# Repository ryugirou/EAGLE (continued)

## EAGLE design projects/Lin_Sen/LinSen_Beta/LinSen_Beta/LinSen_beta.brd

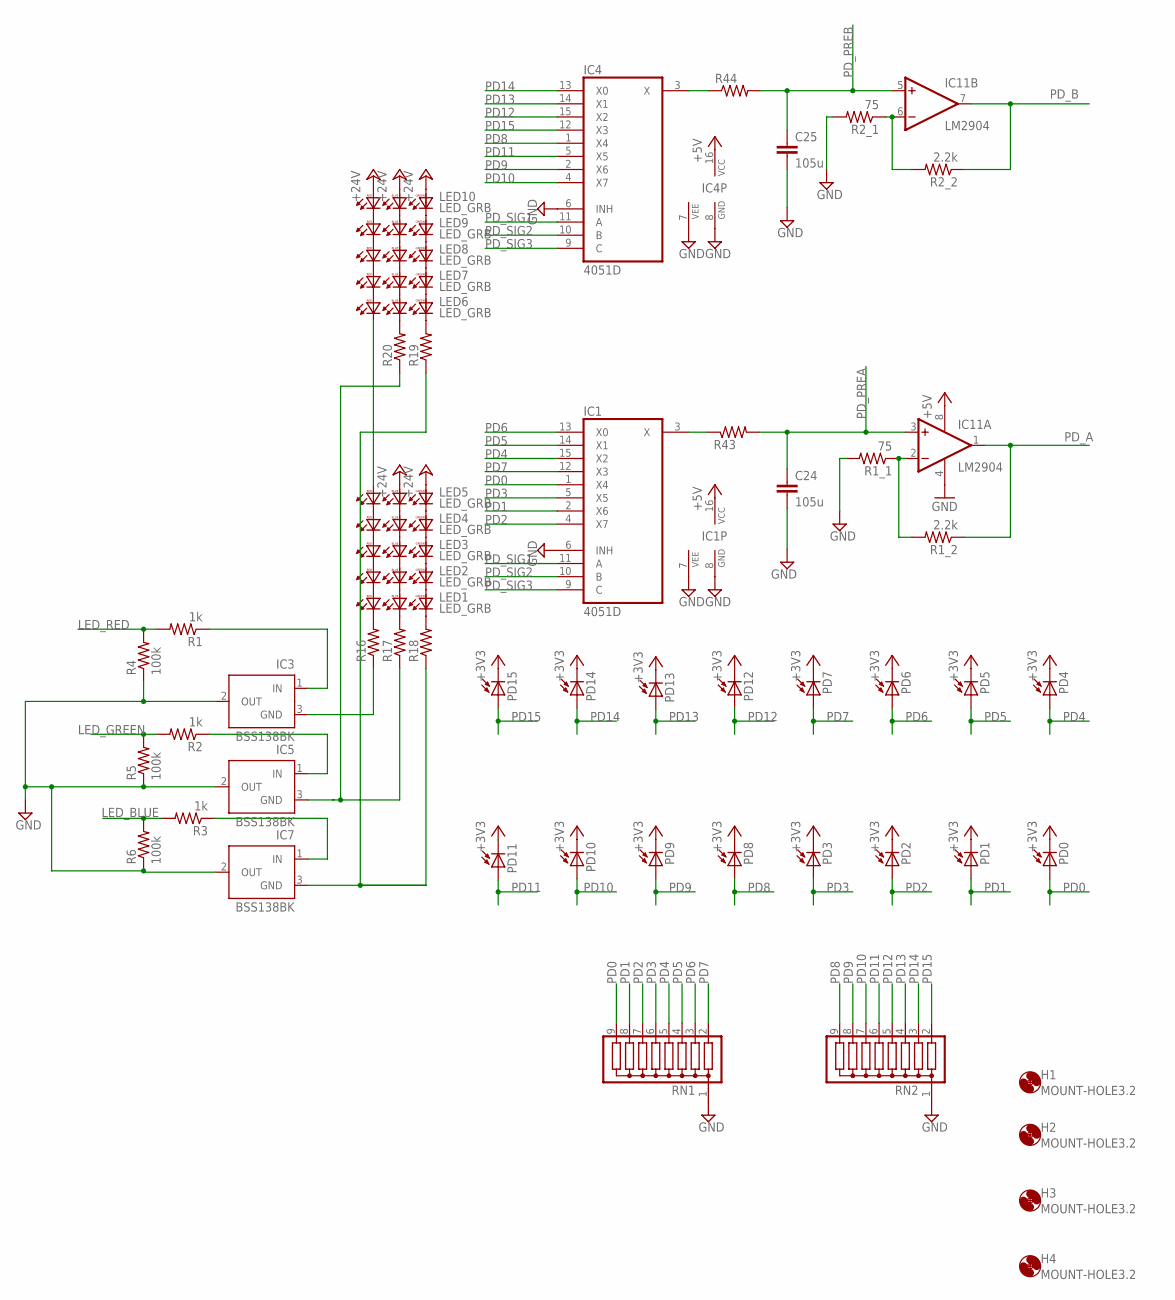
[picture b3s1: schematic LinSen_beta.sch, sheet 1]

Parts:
C24, C25: 105u; C0805
H1, H2, H3, H4: MOUNT-HOLE3.2; 3,2
IC1, IC4: 4051D; SO16
IC3, IC5, IC7: BSS138BK; SOT23
IC11: LM2904; SO08
LED1, LED2, LED3, LED4, LED5, LED6, LED7, LED8, LED9, LED10: LED_GRB
PD0, PD1, PD2, PD3, PD4, PD5, PD6, PD7, PD8, PD9, PD10, PD11, PD12, PD13, PD14, PD15: PDSFH229; SFH229
R1, R2, R3: 1k; R0603
R1_1, R2_1: 75; R0603
R1_2, R2_2: 2.2k; R0603
R4, R5, R6: 100k; R0603
R16, R17, R18, R19, R20, R43, R44: R-US_R0603; R0603
RN1, RN2: G08R; SIL9

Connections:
+3V3: PD0.K (C), PD1.K (C), PD2.K (C), PD3.K (C), PD4.K (C), PD5.K (C), PD6.K (C), PD7.K (C), PD8.K (C), PD9.K (C), PD10.K (C), PD11.K (C), PD12.K (C), PD13.K (C), PD14.K (C), PD15.K (C); also elsewhere on the board
+5V: IC1.16 (VCC), IC4.16 (VCC), IC11.8 (V+); also elsewhere on the board
+24V: LED5.BA, LED5.GA, LED10.BA, LED10.GA, LED10.RA; also elsewhere on the board
GND: C24.2, C25.2, IC1.6 (INH), IC1.7 (VEE), IC1.8 (GND), IC3.2 (OUT), IC4.6 (INH), IC4.7 (VEE), IC4.8 (GND), IC5.2 (OUT), IC7.2 (OUT), IC11.4 (V-), R1_1.2, R2_1.2, R4.1, R5.1, R6.1, RN1.1, RN2.1; also elsewhere on the board
LED_BLUE: R3.2, R6.2; also elsewhere on the board
LED_GREEN: R2.2, R5.2; also elsewhere on the board
LED_RED: R1.2, R4.2; also elsewhere on the board
unnamed: LED1.BA, LED2.BC
unnamed: LED1.GA, LED2.GC
unnamed: LED1.RA, LED2.RC
unnamed: LED2.BA, LED3.BC
unnamed: IC11.6 (-IN), R2_1.1, R2_2.2
unnamed: LED2.GA, LED3.GC
unnamed: LED2.RA, LED3.RC
unnamed: IC11.2 (-IN), R1_1.1, R1_2.2
unnamed: LED3.BA, LED4.BC
unnamed: LED3.GA, LED4.GC
unnamed: LED3.RA, LED4.RC
unnamed: LED4.BA, LED5.BC
unnamed: LED4.GA, LED5.GC
unnamed: LED4.RA, LED5.RC
unnamed: LED1.RC, R16.2
unnamed: LED1.GC, R17.2
unnamed: LED5.RA, LED6.RC
unnamed: LED6.BA, LED7.BC
unnamed: LED6.GA, LED7.GC
unnamed: LED6.RA, LED7.RC
unnamed: LED7.BA, LED8.BC
unnamed: LED7.GA, LED8.GC
unnamed: LED7.RA, LED8.RC
unnamed: LED8.BA, LED9.BC
unnamed: LED8.GA, LED9.GC
unnamed: LED8.RA, LED9.RC
unnamed: LED9.BA, LED10.BC
unnamed: LED9.GA, LED10.GC
unnamed: LED9.RA, LED10.RC
unnamed: IC4.3 (X), R44.1
unnamed: LED1.BC, R18.2
unnamed: IC1.3 (X), R43.1
unnamed: LED6.GC, R20.2
unnamed: LED6.BC, R19.2
unnamed: IC5.3 (GND), R17.1, R20.1
unnamed: IC3.1 (IN), R1.1
unnamed: IC3.3 (GND), R16.1
unnamed: IC5.1 (IN), R2.1
unnamed: IC7.3 (GND), R18.1, R19.1
unnamed: IC7.1 (IN), R3.1
PD0: IC1.1 (X4), PD0.A, RN1.9
PD1: IC1.2 (X6), PD1.A, RN1.8
PD2: IC1.4 (X7), PD2.A, RN1.7
PD3: IC1.5 (X5), PD3.A, RN1.6
PD4: IC1.15 (X2), PD4.A, RN1.5
PD5: IC1.14 (X1), PD5.A, RN1.4
PD6: IC1.13 (X0), PD6.A, RN1.3
PD7: IC1.12 (X3), PD7.A, RN1.2
PD8: IC4.1 (X4), PD8.A, RN2.9
PD9: IC4.2 (X6), PD9.A, RN2.8
PD10: IC4.4 (X7), PD10.A, RN2.7
PD11: IC4.5 (X5), PD11.A, RN2.6
PD12: IC4.15 (X2), PD12.A, RN2.5
PD13: IC4.14 (X1), PD13.A, RN2.4
PD14: IC4.13 (X0), PD14.A, RN2.3
PD15: IC4.12 (X3), PD15.A, RN2.2
PD_A: IC11.1 (OUT), R1_2.1; also elsewhere on the board
PD_B: IC11.7 (OUT), R2_2.1; also elsewhere on the board
PD_PREA: C24.1, IC11.3 (+IN), R43.2; also elsewhere on the board
PD_PREB: C25.1, IC11.5 (+IN), R44.2; also elsewhere on the board
PD_SIG1: IC1.11 (A), IC4.11 (A); also elsewhere on the board
PD_SIG2: IC1.10 (B), IC4.10 (B); also elsewhere on the board
PD_SIG3: IC1.9 (C), IC4.9 (C); also elsewhere on the board

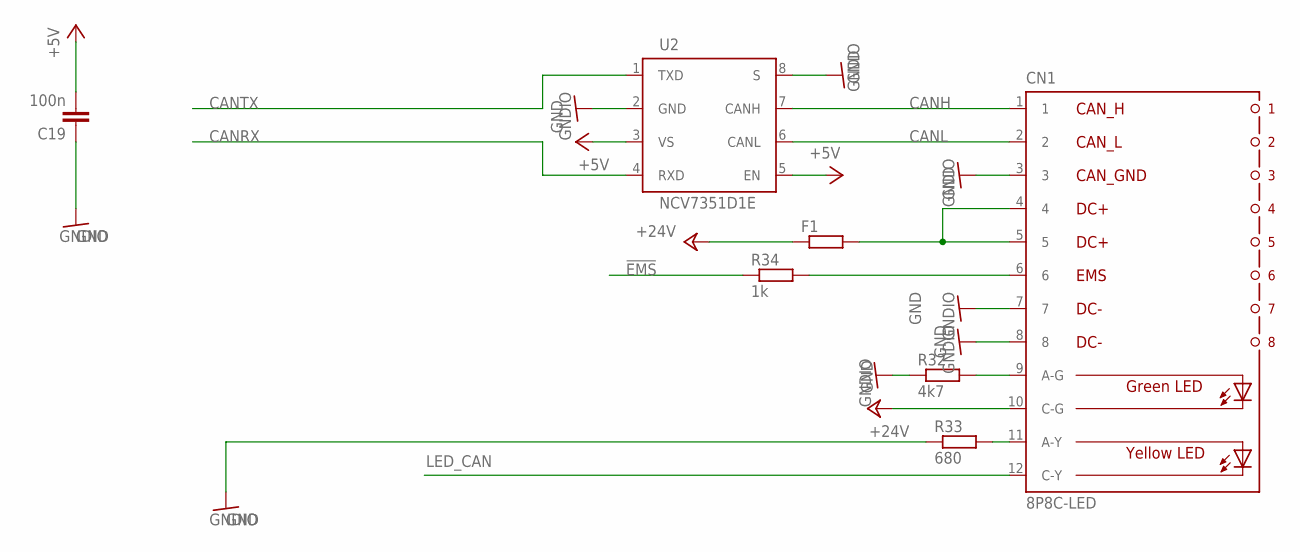
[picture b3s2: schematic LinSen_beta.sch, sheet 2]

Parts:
C19: 100n; C0603
CN1: 8P8C-LED
F1: R-EU_R1206; R1206
R32: 4k7; R0603
R33: 680; R0603
R34: 1k; R0603
U2: NCV7351D1E; SO08

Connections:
!EMS: R34.1; also elsewhere on the board
!EMS_ISO: CN1.6, R34.2
+5V: C19.2, U2.3 (VS), U2.5 (EN); also elsewhere on the board
+24V: CN1.10 (C-G), F1.1; also elsewhere on the board
CANH: CN1.1, U2.7 (CANH)
CANL: CN1.2, U2.6 (CANL)
CANRX: U2.4 (RXD); also elsewhere on the board
CANTX: U2.1 (TXD); also elsewhere on the board
GND: C19.1, CN1.3, CN1.7, CN1.8, R32.1, R33.1, U2.2 (GND), U2.8 (S); also elsewhere on the board
LED_CAN: CN1.12 (C-Y); also elsewhere on the board
unnamed: CN1.9 (A-G), R32.2
unnamed: CN1.11 (A-Y), R33.2
unnamed: CN1.4, CN1.5, F1.2

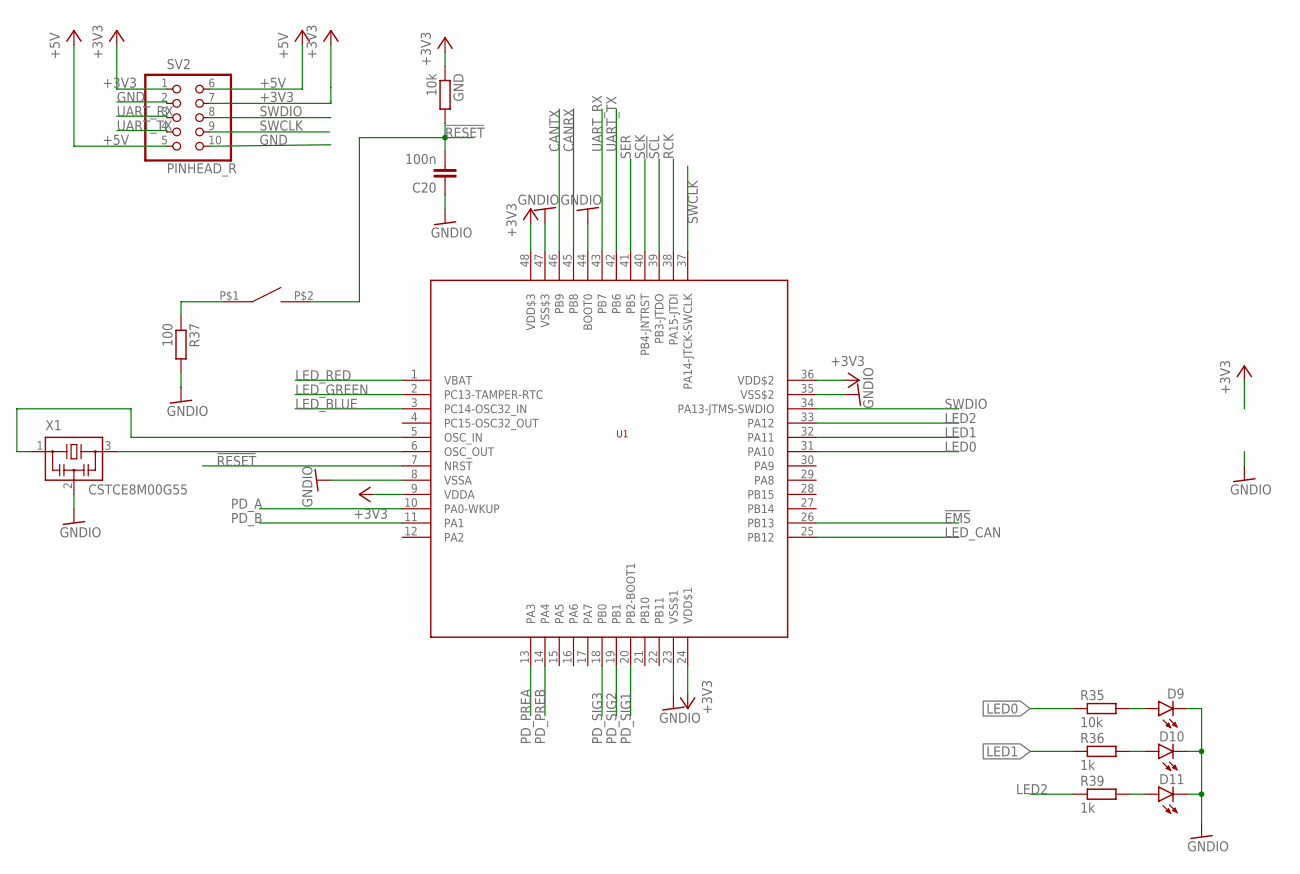
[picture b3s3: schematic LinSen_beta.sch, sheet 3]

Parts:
C20: 100n; C0603
D9, D10, D11: LEDCHIPLED_0805; CHIPLED_0805
GND: 10k; R0603
R35: 10k; R0603
R36, R39: 1k; R0603
R37: 100; R0603
SV2: PINHEAD_R; PINHEDA_R
SW1: SWITCH_TACTILETOP; SWITCH_TACTILE_3X6
U1: STM32F103C8; LQFP48
X1: CSTCE8M00G55

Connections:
!EMS: U1.26 (PB13); also elsewhere on the board
!RESET: C20.2, GND.2, SW1.P$2 (2), U1.7 (NRST)
!SCL: U1.39 (PB3-JTDO); also elsewhere on the board
+3V3: GND.1, SV2.1, SV2.7, U1.9 (VDDA), U1.24 (VDD$1), U1.36 (VDD$2), U1.48 (VDD$3); also elsewhere on the board
+5V: SV2.5, SV2.6; also elsewhere on the board
CANRX: U1.45 (PB8); also elsewhere on the board
CANTX: U1.46 (PB9); also elsewhere on the board
GND: C20.1, D9.C, D10.C, D11.C, R37.2, SV2.2, SV2.10, U1.8 (VSSA), U1.23 (VSS$1), U1.35 (VSS$2), U1.44 (BOOT0), U1.47 (VSS$3), X1.2; also elsewhere on the board
LED0: R35.1, U1.31 (PA10)
LED1: R36.1, U1.32 (PA11)
LED2: R39.1, U1.33 (PA12)
LED_BLUE: U1.3 (PC14-OSC32_IN); also elsewhere on the board
LED_CAN: U1.25 (PB12); also elsewhere on the board
LED_GREEN: U1.2 (PC13-TAMPER-RTC); also elsewhere on the board
LED_RED: U1.1 (VBAT); also elsewhere on the board
unnamed: D10.A, R36.2
unnamed: D9.A, R35.2
unnamed: U1.6 (OSC_OUT), X1.3
unnamed: U1.5 (OSC_IN), X1.1
unnamed: R37.1, SW1.P$1 (1)
unnamed: D11.A, R39.2
PD_A: U1.10 (PA0-WKUP); also elsewhere on the board
PD_B: U1.11 (PA1); also elsewhere on the board
PD_PREA: U1.13 (PA3); also elsewhere on the board
PD_PREB: U1.14 (PA4); also elsewhere on the board
PD_SIG1: U1.20 (PB2-BOOT1); also elsewhere on the board
PD_SIG2: U1.19 (PB1); also elsewhere on the board
PD_SIG3: U1.18 (PB0); also elsewhere on the board
RCK: U1.38 (PA15-JTDI); also elsewhere on the board
SCK: U1.40 (PB4-JNTRST); also elsewhere on the board
SER: U1.41 (PB5); also elsewhere on the board
SWCLK: SV2.9, U1.37 (PA14-JTCK-SWCLK)
SWDIO: SV2.8, U1.34 (PA13-JTMS-SWDIO)
UART_RX: SV2.3, U1.43 (PB7)
UART_TX: SV2.4, U1.42 (PB6)

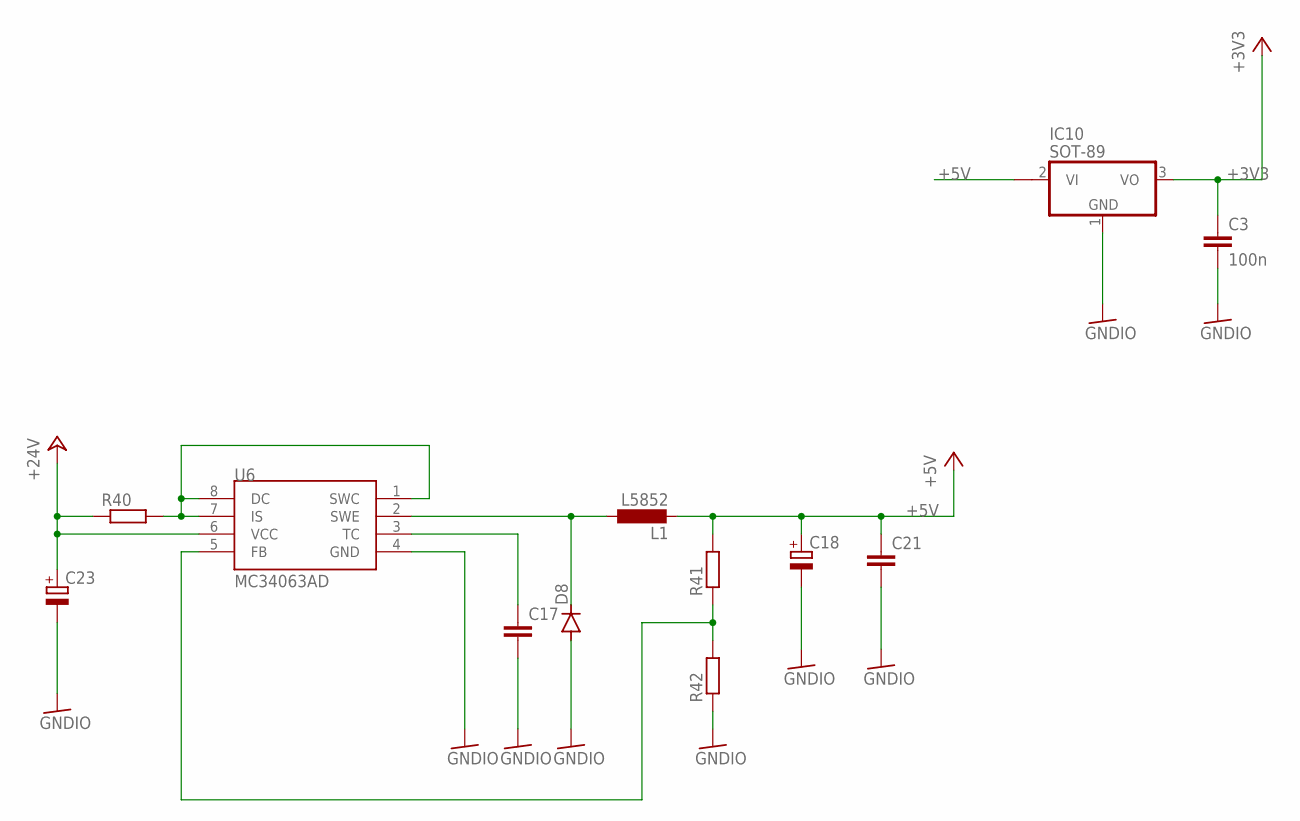
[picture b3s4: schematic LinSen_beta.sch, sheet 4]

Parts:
C3: 100n; C0603
C17, C21: C-EUC0603; C0603
C18, C23: CPOL-EUE2-5; E2-5
D8: DIODE-SOD123; SOD123
IC10: SOT-89; SOT89
L1: L5852
R40: R-EU_R1206; R1206
R41, R42: R-EU_R0603; R0603
U6: MC34063AD; SOIC8

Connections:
+3V3: C3.1, IC10.3 (VO); also elsewhere on the board
+5V: C18.+, C21.1, IC10.2@1 (VI1), L1.P$2 (2), R41.2; also elsewhere on the board
+24V: C23.+, R40.1, U6.6 (VCC); also elsewhere on the board
GND: C3.2, C17.2, C18.-, C21.2, C23.-, D8.A, IC10.1 (GND), R42.1, U6.4 (GND); also elsewhere on the board
unnamed: R40.2, U6.1 (SWC), U6.7 (IS), U6.8 (DC)
unnamed: D8.C, L1.P$1 (1), U6.2 (SWE)
unnamed: C17.1, U6.3 (TC)
unnamed: R41.1, R42.2, U6.5 (FB)

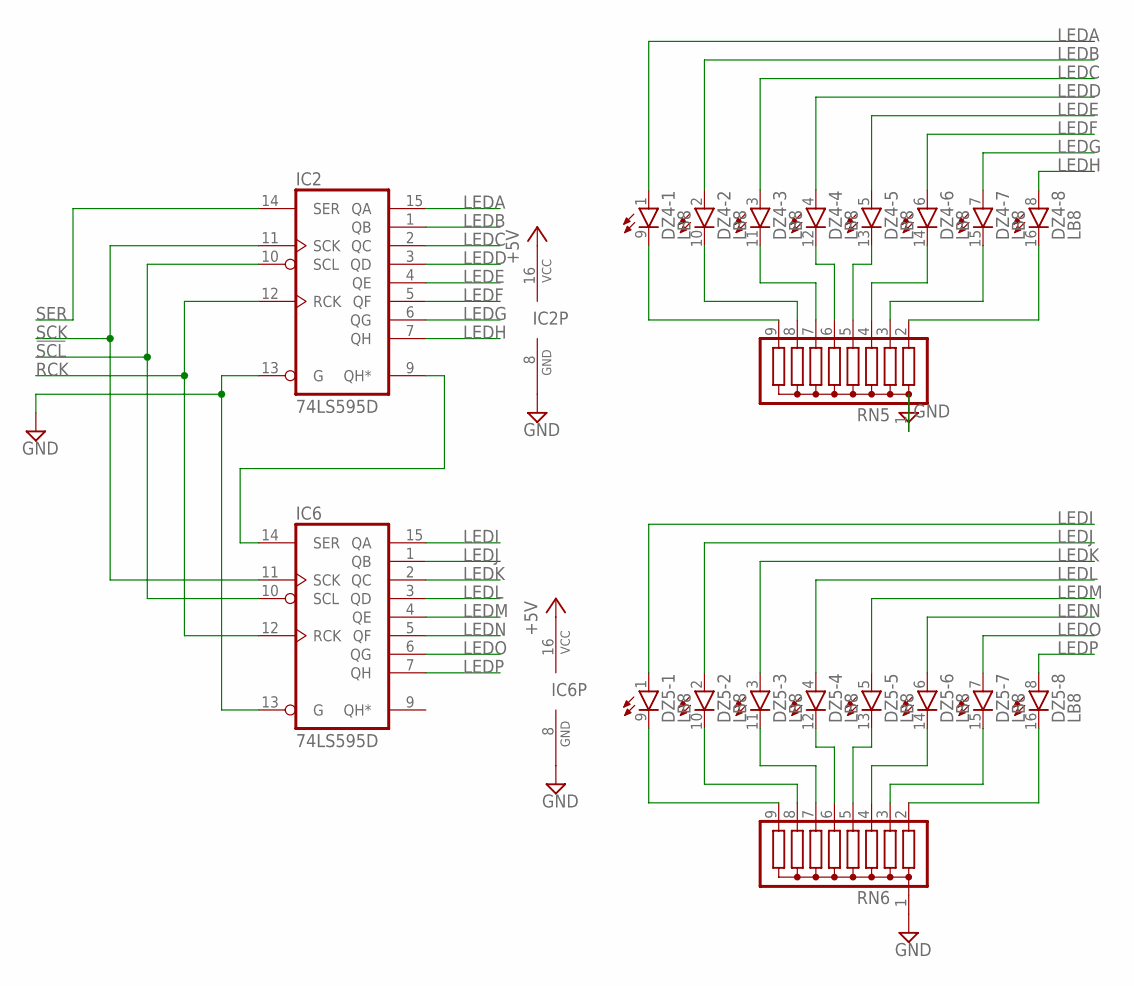
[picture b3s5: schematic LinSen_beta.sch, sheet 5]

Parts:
DZ4, DZ5: LB8
IC2, IC6: 74LS595D; SO16
RN5, RN6: G08R; SIL9

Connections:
!SCL: IC2.10 (SCL), IC6.10 (SCL); also elsewhere on the board
+5V: IC2.16 (VCC), IC6.16 (VCC); also elsewhere on the board
GND: IC2.8 (GND), IC2.13 (G), IC6.8 (GND), IC6.13 (G), RN5.1, RN6.1; also elsewhere on the board
LEDA: DZ4.1 (A), IC2.15 (QA)
LEDB: DZ4.2 (A), IC2.1 (QB)
LEDC: DZ4.3 (A), IC2.2 (QC)
LEDD: DZ4.4 (A), IC2.3 (QD)
LEDE: DZ4.5 (A), IC2.4 (QE)
LEDF: DZ4.6 (A), IC2.5 (QF)
LEDG: DZ4.7 (A), IC2.6 (QG)
LEDH: DZ4.8 (A), IC2.7 (QH)
LEDI: DZ5.1 (A), IC6.15 (QA)
LEDJ: DZ5.2 (A), IC6.1 (QB)
LEDK: DZ5.3 (A), IC6.2 (QC)
LEDL: DZ5.4 (A), IC6.3 (QD)
LEDM: DZ5.5 (A), IC6.4 (QE)
LEDN: DZ5.6 (A), IC6.5 (QF)
LEDO: DZ5.7 (A), IC6.6 (QG)
LEDP: DZ5.8 (A), IC6.7 (QH)
unnamed: IC2.9 (QH*), IC6.14 (SER)
unnamed: DZ4.9 (C), RN5.9
unnamed: DZ4.10 (C), RN5.8
unnamed: DZ4.11 (C), RN5.7
unnamed: DZ4.12 (C), RN5.6
unnamed: DZ4.13 (C), RN5.5
unnamed: DZ4.14 (C), RN5.4
unnamed: DZ4.15 (C), RN5.3
unnamed: DZ4.16 (C), RN5.2
unnamed: DZ5.12 (C), RN6.6
unnamed: DZ5.11 (C), RN6.7
unnamed: DZ5.10 (C), RN6.8
unnamed: DZ5.9 (C), RN6.9
unnamed: DZ5.13 (C), RN6.5
unnamed: DZ5.14 (C), RN6.4
unnamed: DZ5.15 (C), RN6.3
unnamed: DZ5.16 (C), RN6.2
RCK: IC2.12 (RCK), IC6.12 (RCK); also elsewhere on the board
SCK: IC2.11 (SCK), IC6.11 (SCK); also elsewhere on the board
SER: IC2.14 (SER); also elsewhere on the board

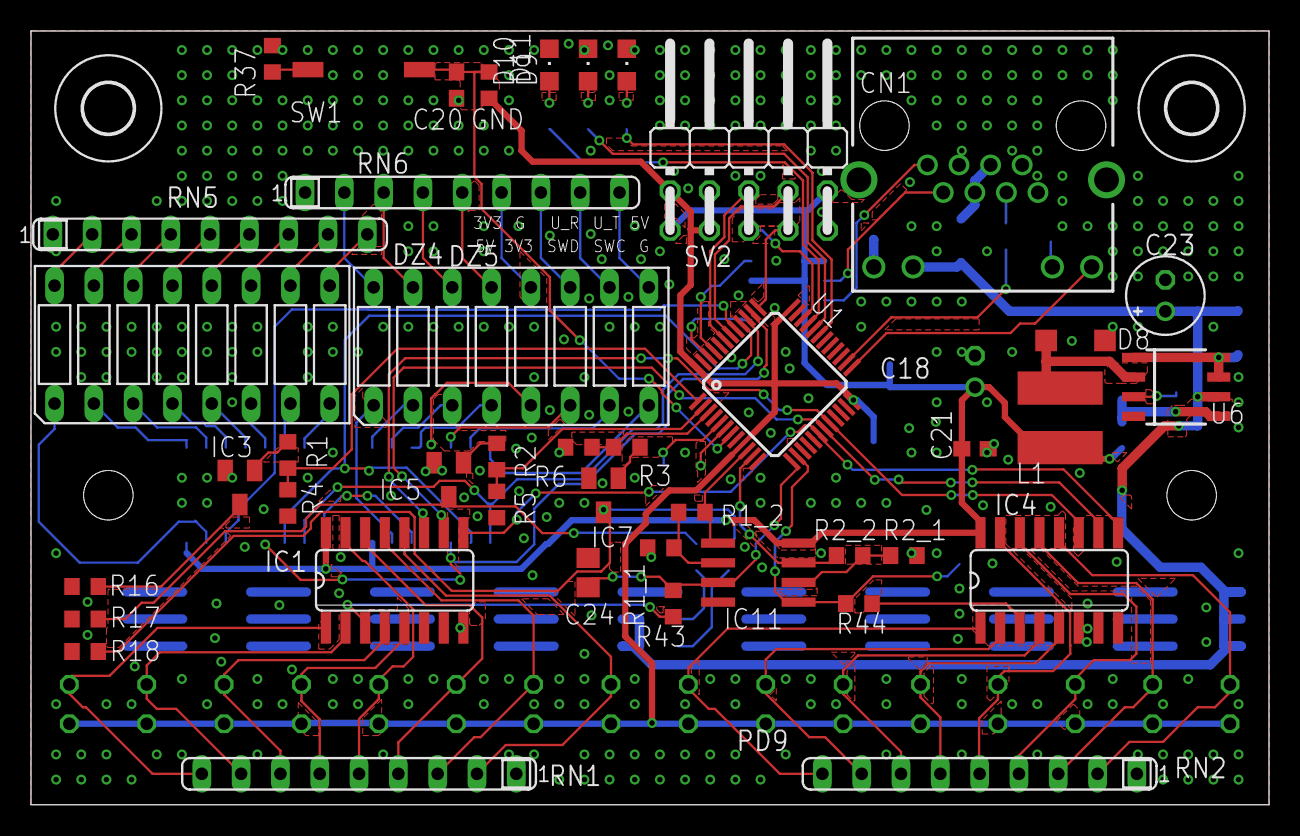
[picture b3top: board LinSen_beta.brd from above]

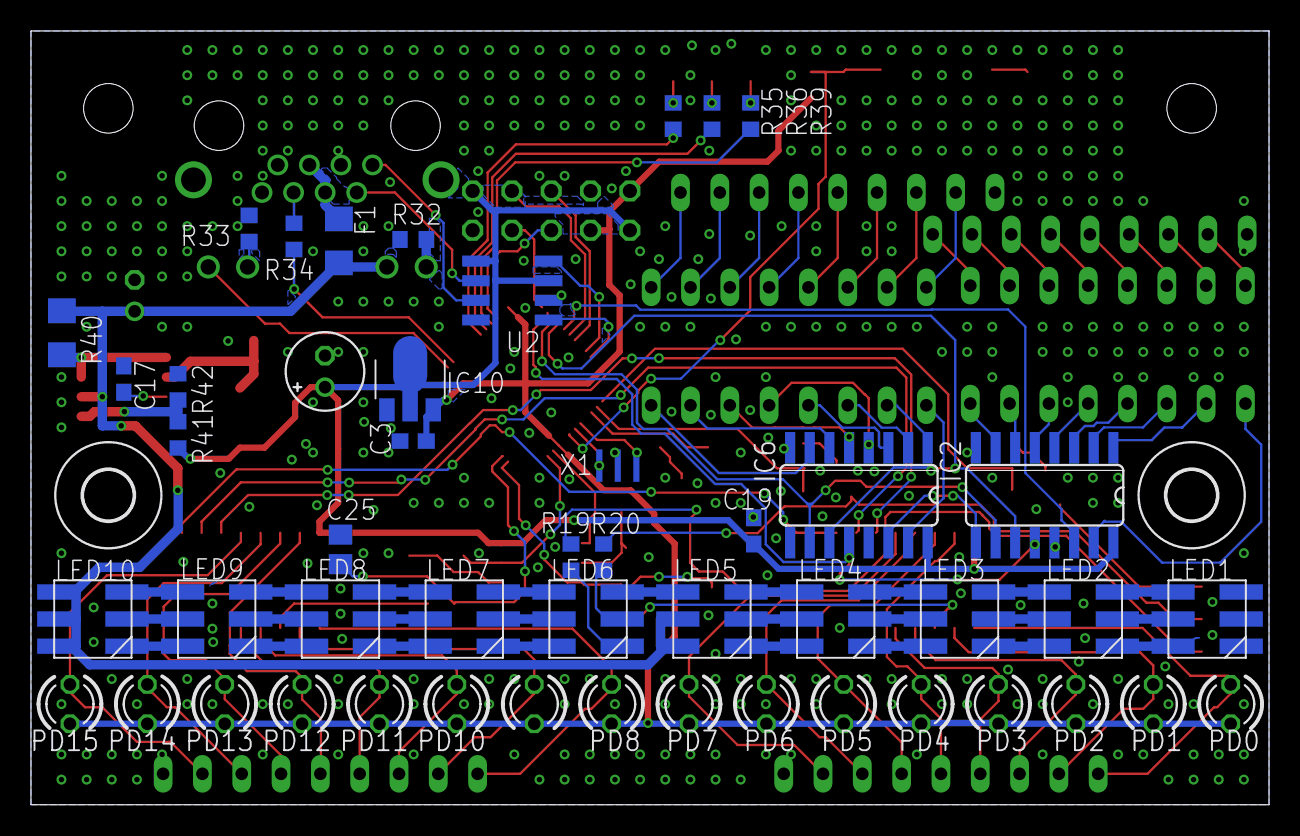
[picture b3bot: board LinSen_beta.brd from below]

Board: 2 copper layers, 80.0 x 50.0 mm, 95 parts (50 on the bottom side), 135 nets.

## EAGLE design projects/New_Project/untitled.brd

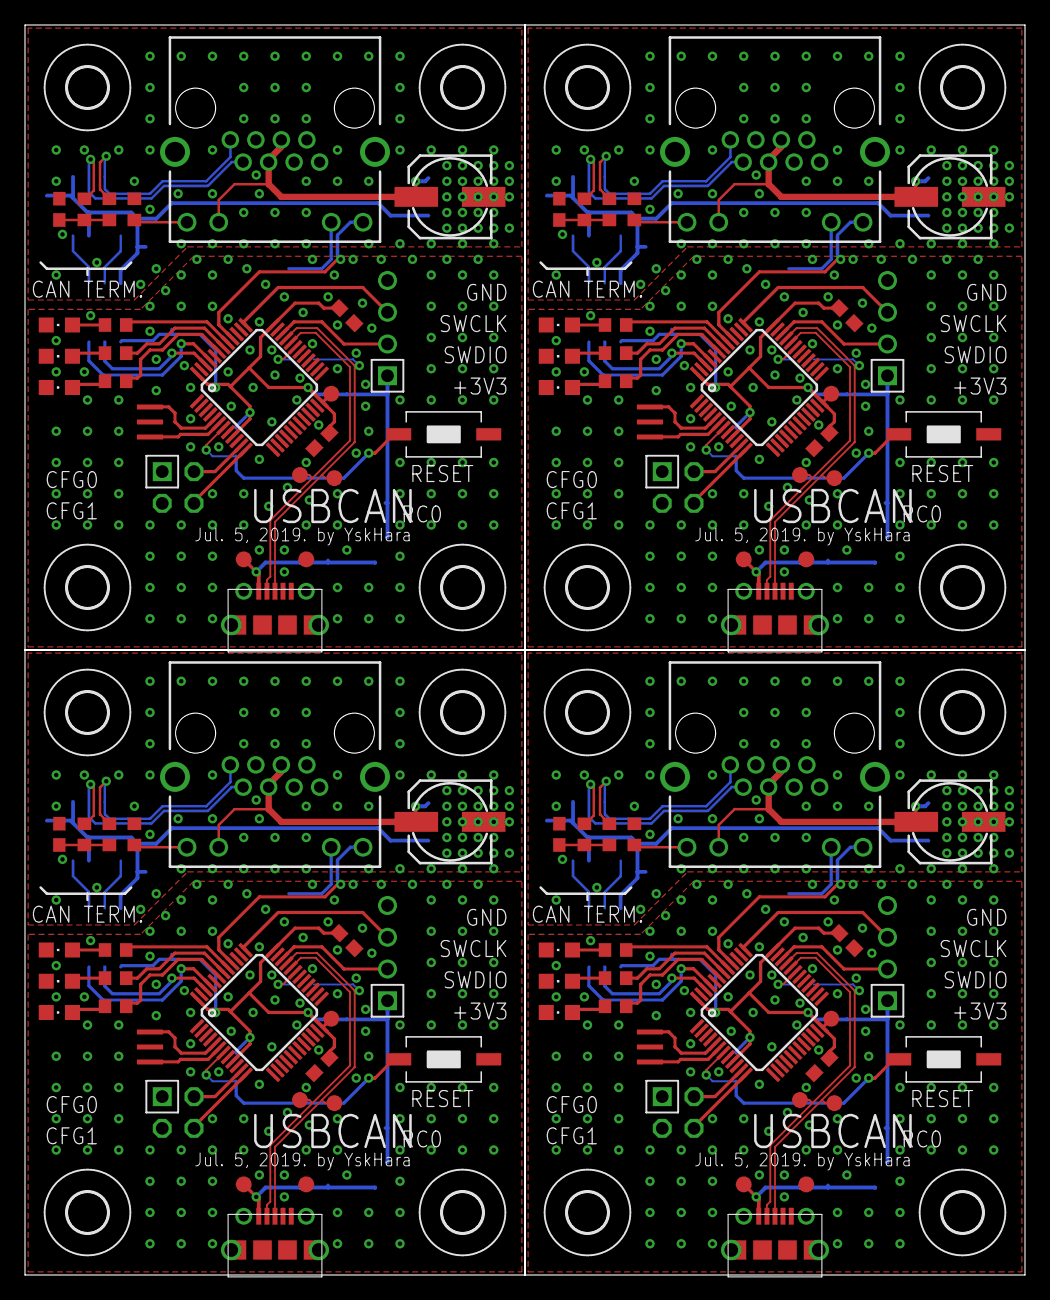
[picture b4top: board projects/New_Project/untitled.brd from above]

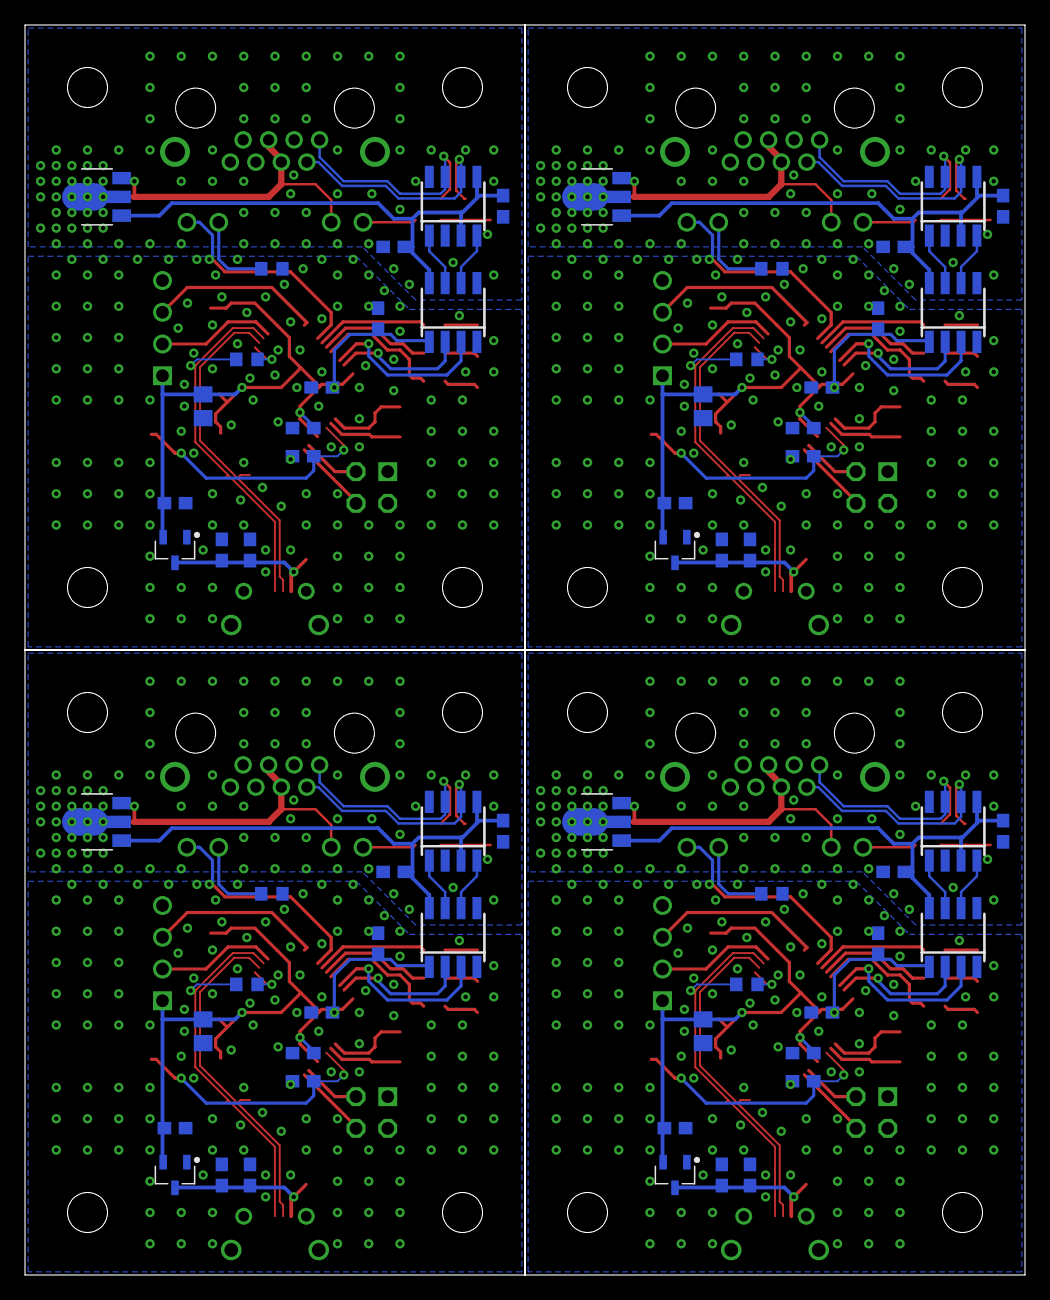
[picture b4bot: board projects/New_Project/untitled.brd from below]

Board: 2 copper layers, 80.0 x 100.0 mm, 180 parts (64 on the bottom side), 128 nets.

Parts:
C1, C16, C30, C44: EEEHA1E220P; 153CLV-0605
C2, C3, C4, C15, C17, C27, C29, C31, C41, C43, C45, C55: C0603
C5, C25, C39, C53: 1u; C0603
C6, C8, C9, C10, C11, C12, C13, C14, C18, C19, C21, C22, C23, C24, C26, C28, C32, C33, C35, C36, C37, C38, C40, C42, C46, C47, C49, C50, C51, C52, C54, C56: 100n; C0603
C7, C20, C34, C48: 4u7; C0805
D1, D2, D3, D4, D5, D6, D7, D8, D9, D10, D11, D12: CHIPLED_0805
H1, H2, H3, H4, H5, H6, H7, H8, H9, H10, H11, H12, H13, H14, H15, H16: MOUNT-HOLE3.2; 3,2
J1, J5, J9, J13: 8P8C-LED
J2, J6, J10, J14: MICRO-USB-RECEPTACLE47589-0001; 47589-0001
J3, J8, J12, J16: MA04-1
J4, J7, J11, J15: MA02-2; MA02-2W
R1, R2, R9, R10, R17, R18, R25, R26: R0603
R3, R4, R11, R15, R19, R23, R27, R31: 60; R0603
R5, R16, R24, R32: 1k5; R0603
R6, R7, R8, R12, R13, R14, R20, R21, R22, R28, R29, R30: 1k; R0603
S1, S2, S3, S4: SWITCH_TACTILETOP; SWITCH_TACTILE_3X6
TP1, TP2, TP3, TP4, TP5, TP6, TP7, TP8, TP9, TP10, TP11, TP12, TP13, TP14, TP15, TP16, TP17, TP18, TP19, TP20: TPB1,27; B1,27
U1, U7, U12, U17: STM32F302C; LQFP48
U2, U6, U11, U16: NCV7351D1E; SO08
U3, U8, U13, U18: SI8621AB-B-IS; SO08
U4, U9, U14, U19: AP2127N-3.3TRG1; SOT95P240X110-3
U5, U10, U15, U20: 78L05F; SOT89
X1, X2, X3, X4: CSTCE8M00G55

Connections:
!RESET: C14.2, S1.P$2, U1.7
!RESET1: C24.2, S2.P$2, U7.7
!RESET2: C38.2, S3.P$2, U12.7
!RESET3: C52.2, S4.P$2, U17.7
+3V1: C19.1, C20.1, C21.2, C22.2, C23.2, C26.2, C28.2, J8.1, TP7.TP, U7.9, U7.24, U7.36, U7.48, U8.1, U9.2
+3V2: C33.1, C34.1, C35.2, C36.2, C37.2, C40.2, C42.2, J12.1, TP12.TP, U12.9, U12.24, U12.36, U12.48, U13.1, U14.2
+3V3: C7.1, C8.1, C9.2, C10.2, C11.2, C12.2, C13.2, J3.1, TP2.TP, U1.9, U1.24, U1.36, U1.48, U3.1, U4.2
+3V4: C47.1, C48.1, C49.2, C50.2, C51.2, C54.2, C56.2, J16.1, TP17.TP, U17.9, U17.24, U17.36, U17.48, U18.1, U19.2
+5V: C5.1, C6.1, J2.1, TP3.TP, U4.3
+5V1: C18.1, C25.1, J6.1, TP8.TP, U9.3
+5V2: C32.1, C39.1, J10.1, TP13.TP, U14.3
+5V3: C46.1, C53.1, J14.1, TP18.TP, U19.3
+5V_ISO: C3.1, C4.1, U2.3, U2.5, U3.8, U5.1
+5V_ISO1: C15.1, C17.1, U6.3, U6.5, U8.8, U10.1
+5V_ISO2: C29.1, C31.1, U11.3, U11.5, U13.8, U15.1
+5V_ISO3: C43.1, C45.1, U16.3, U16.5, U18.8, U20.1
+12V: C1.+, J1.4, J1.5, J1.GA, U5.3
+12V1: C16.+, J5.4, J5.5, J5.GA, U10.3
+12V2: C30.+, J9.4, J9.5, J9.GA, U15.3
+12V3: C44.+, J13.4, J13.5, J13.GA, U20.3
CANH: J1.1, R4.1, U2.7
CANH1: J5.1, R11.1, U6.7
CANH2: J9.1, R19.1, U11.7
CANH3: J13.1, R27.1, U16.7
CANL: J1.2, R3.1, U2.6
CANL1: J5.2, R15.1, U6.6
CANL2: J9.2, R23.1, U11.6
CANL3: J13.2, R31.1, U16.6
CANRX: U1.45, U3.3
CANRX1: U7.45, U8.3
CANRX2: U12.45, U13.3
CANRX3: U17.45, U18.3
CANRX_ISO: U2.4, U3.6
CANRX_ISO1: U6.4, U8.6
CANRX_ISO2: U11.4, U13.6
CANRX_ISO3: U16.4, U18.6
CANTX: U1.46, U3.2
CANTX1: U7.46, U8.2
CANTX2: U12.46, U13.2
CANTX3: U17.46, U18.2
CANTX_ISO: U2.1, U3.7
CANTX_ISO1: U6.1, U8.7
CANTX_ISO2: U11.1, U13.7
CANTX_ISO3: U16.1, U18.7
CAN_LED: J1.YA, U1.40
CAN_LED1: J5.YA, U7.40
CAN_LED2: J9.YA, U12.40
CAN_LED3: J13.YA, U17.40
CONF0: J4.3, U1.11
CONF1: J4.1, U1.12
CONF2: J7.3, U7.11
CONF3: J7.1, U7.12
CONF4: J11.3, U12.11
CONF5: J11.1, U12.12
CONF6: J15.3, U17.11
CONF7: J15.1, U17.12
GNDA: C5.2, C6.2, C7.2, C8.2, C9.1, C10.1, C11.1, C12.1, C13.1, C14.1, D1.C, D2.C, D3.C, J2.4, J2.5, J2.CASING1, J2.CASING2, J2.CASING3, J2.CASING4, J2.P$1, J2.P$2, J2.P$3, J2.P$4, J3.4, J4.2, J4.4, R2.1, S1.P$1, TP1.TP, U1.8, U1.23, U1.35, U1.44, U1.47, U3.4, U4.1, X1.2
GNDA1: C18.2, C19.2, C20.2, C21.1, C22.1, C23.1, C24.1, C25.2, C26.1, C28.1, D4.C, D5.C, D6.C, J6.4, J6.5, J6.CASING1, J6.CASING2, J6.CASING3, J6.CASING4, J6.P$1, J6.P$2, J6.P$3, J6.P$4, J7.2, J7.4, J8.4, R10.1, S2.P$1, TP6.TP, U7.8, U7.23, U7.35, U7.44, U7.47, U8.4, U9.1, X2.2
GNDA2: C32.2, C33.2, C34.2, C35.1, C36.1, C37.1, C38.1, C39.2, C40.1, C42.1, D7.C, D8.C, D9.C, J10.4, J10.5, J10.CASING1, J10.CASING2, J10.CASING3, J10.CASING4, J10.P$1, J10.P$2, J10.P$3, J10.P$4, J11.2, J11.4, J12.4, R18.1, S3.P$1, TP11.TP, U12.8, U12.23, U12.35, U12.44, U12.47, U13.4, U14.1, X3.2
GNDA3: C46.2, C47.2, C48.2, C49.1, C50.1, C51.1, C52.1, C53.2, C54.1, C56.1, D10.C, D11.C, D12.C, J14.4, J14.5, J14.CASING1, J14.CASING2, J14.CASING3, J14.CASING4, J14.P$1, J14.P$2, J14.P$3, J14.P$4, J15.2, J15.4, J16.4, R26.1, S4.P$1, TP16.TP, U17.8, U17.23, U17.35, U17.44, U17.47, U18.4, U19.1, X4.2
GNDIO: C1.-, C2.2, C3.2, C4.2, J1.3, J1.7, J1.8, J1.M1, J1.M2, R1.1, U2.2, U2.8, U3.5, U5.2, U5.2@1
GNDIO1: C15.2, C16.-, C17.2, C27.2, J5.3, J5.7, J5.8, J5.M1, J5.M2, R9.1, U6.2, U6.8, U8.5, U10.2, U10.2@1
GNDIO2: C29.2, C30.-, C31.2, C41.2, J9.3, J9.7, J9.8, J9.M1, J9.M2, R17.1, U11.2, U11.8, U13.5, U15.2, U15.2@1
GNDIO3: C43.2, C44.-, C45.2, C55.2, J13.3, J13.7, J13.8, J13.M1, J13.M2, R25.1, U16.2, U16.8, U18.5, U20.2, U20.2@1
LED0: R6.1, U1.41
LED1: R7.1, U1.42
LED2: R8.1, U1.43
LED3: R14.1, U7.43
LED4: R12.1, U7.41
LED5: R13.1, U7.42
LED6: R22.1, U12.43
LED7: R20.1, U12.41
LED8: R21.1, U12.42
LED9: R30.1, U17.43
LED10: R28.1, U17.41
LED11: R29.1, U17.42
unnamed: J5.GC, R9.2
unnamed: D2.A, R7.2
unnamed: J1.GC, R1.2
unnamed: J1.YC, R2.2
unnamed: D1.A, R6.2
unnamed: C2.1, R3.2, R4.2
unnamed: U1.6, X1.3
unnamed: U1.5, X1.1
unnamed: J5.YC, R10.2
unnamed: U7.6, X2.3
unnamed: R5.1, U1.31
unnamed: U7.5, X2.1
unnamed: R16.1, U7.31
unnamed: C27.1, R11.2, R15.2
unnamed: D5.A, R13.2
unnamed: D4.A, R12.2
unnamed: D6.A, R14.2
unnamed: J9.GC, R17.2
unnamed: J9.YC, R18.2
unnamed: U12.6, X3.3
unnamed: D3.A, R8.2
unnamed: U12.5, X3.1
unnamed: R24.1, U12.31
unnamed: C41.1, R19.2, R23.2
unnamed: D8.A, R21.2
unnamed: D7.A, R20.2
unnamed: D9.A, R22.2
unnamed: J13.GC, R25.2
unnamed: J13.YC, R26.2
unnamed: U17.6, X4.3
unnamed: U17.5, X4.1
unnamed: R32.1, U17.31
unnamed: C55.1, R27.2, R31.2
unnamed: D11.A, R29.2
unnamed: D10.A, R28.2
unnamed: D12.A, R30.2
SWCLK: J3.3, U1.37
SWCLK1: J8.3, U7.37
SWCLK2: J12.3, U12.37
SWCLK3: J16.3, U17.37
SWDIO: J3.2, U1.34
SWDIO1: J8.2, U7.34
SWDIO2: J12.2, U12.34
SWDIO3: J16.2, U17.34
USB_DM: J2.2, TP4.TP, U1.32
USB_DM1: J6.2, TP9.TP, U7.32
USB_DM2: J10.2, TP14.TP, U12.32
USB_DM3: J14.2, TP19.TP, U17.32
USB_DP: J2.3, R5.2, TP5.TP, U1.33
USB_DP1: J6.3, R16.2, TP10.TP, U7.33
USB_DP2: J10.3, R24.2, TP15.TP, U12.33
USB_DP3: J14.3, R32.2, TP20.TP, U17.33
